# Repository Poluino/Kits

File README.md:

# WeatherStationPCB 

This repository includes all the files to print your own PCB, Source the components, and debug the circuit.

Currently we offer 4 different kits;

# Kits:
1. Barebones Kit: 
    - Temperature, Humidity, and Pressure. The three basic measurements for a home weather station project.
    - Version 1.0 Includes the BME280 sensor and an ESP32 Dev Board (30 pin).
  
2. Full Kit:
    - Temperature, Humidity, Pressure, Air Quality, Luminosity, UV Index, and Rain.
    - Version 1.2 Includes the DHT11 for Humidity, BMP280 for Pressure and Temperature, MQ - 135 for Air Quality, BH1750 for Luminosity, GUVA - S12SD for UV Index, and YL - 83 for Rain.
    - Version 2.0 Will use BME280 for Humidity, Temperature, and Humidity, VEML 6070 for UV Index. Others will remain Unchanged.
  
3. Full Kit (SMD version):
    - Basically the big boy version of the Full Kit, which uses the same sensors used by the Full Kit (V - 2.0) but will have all the components in their SMD package and will include components for a DIY ESP32 Development Board. 

4. Extended: 
    - This is for the Real DIY Weatherman. It includes a ton of high accuracy sensors for Temperature, Humidity, Pressure, Air Quality, Carbon Monoxide, Carbon Dioxide, Wind Speed, Wind Direction, Rain Gauge, UV Index, Luminosity, Soil Moisture, Ground Temperature

The PCBs for the kits were designed using the KiCad Open source software. 

# You can purchase our Kits at our Tindie Store:
 - [India](https://www.tindie.com/stores/wsp_india/)

Feel free to contact me via email at dhruv@weatherstationproject.com or via discord at DhruvS#7149.

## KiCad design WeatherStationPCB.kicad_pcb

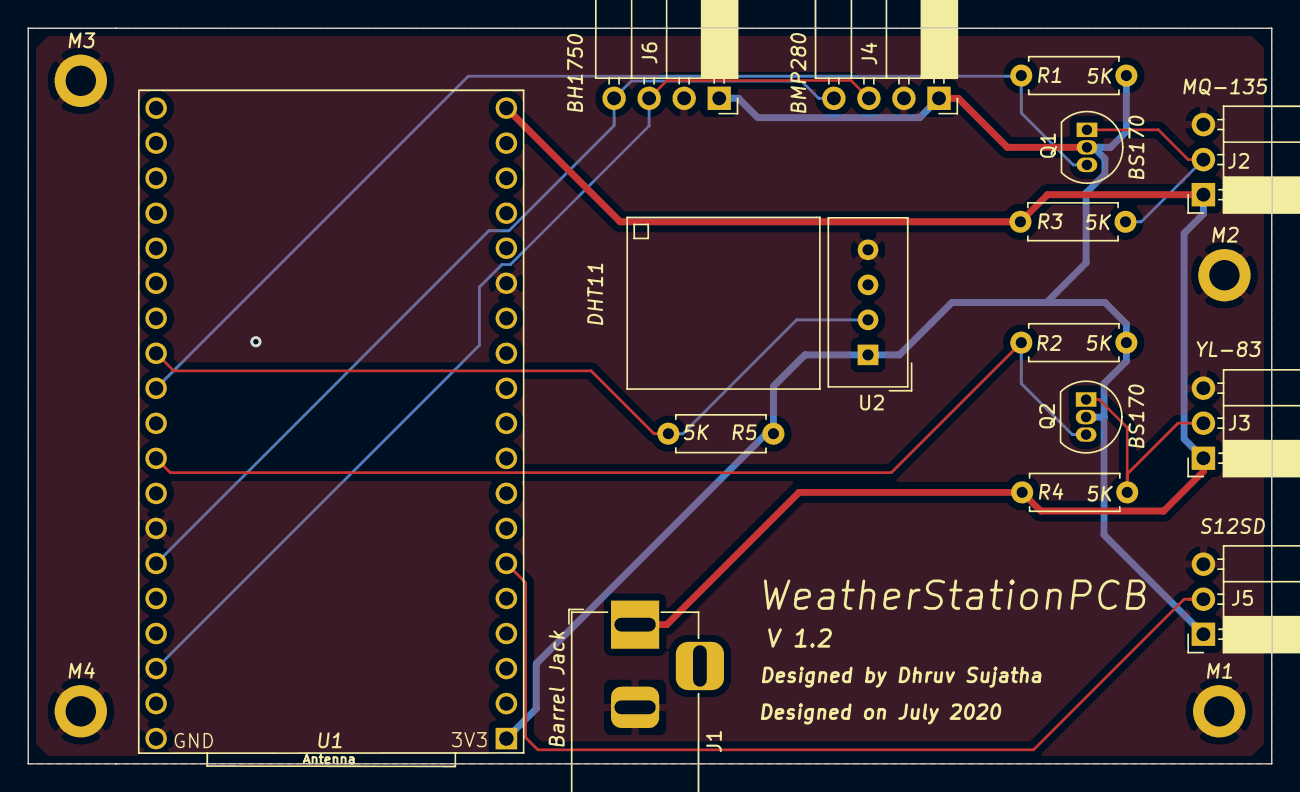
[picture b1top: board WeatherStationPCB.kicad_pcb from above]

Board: 2 copper layers, 90.2 x 53.3 mm, 19 parts (0 on the bottom side), 11 nets.

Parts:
J1: Barrel_Jack_Switch; BarrelJack_Horizontal
J2, J3, J5: Conn_01x03_Female; PinSocket_1x03_P2.54mm_Horizontal
J4: BMP280 Pressure Sensor; PinSocket_1x04_P2.54mm_Horizontal
J6: BH1750 Lux Meter; PinSocket_1x04_P2.54mm_Horizontal
M1, M2, M3, M4: MountingHole_2.2mm_M2_DIN965_Pad
Q1, Q2: BS170; TO-92_Inline
R1, R2, R3, R4, R5: 5K; R_Axial_DIN0207_L6.3mm_D2.5mm_P7.62mm_Horizontal
U1: ESP32-DEVKITC-32D; MODULE_ESP32-DEVKITC-32D
U2: DHT11; Aosong_DHT11_5.5x12.0_P2.54mm

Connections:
3V3: J4.1, J5.1, J6.1, Q1.2, Q2.2, R1.2, R2.2, R5.1, U1.1, U2.1
5V: J1.1, J2.1, J3.1, R3.1, R4.1, U1.19
DHT22Data: R5.2, U1.31, U2.2
GND: J1.2, J2.3, J3.3, J4.2, J5.3, J6.2, M1.1, M2.2, M3.3, M4.4, U1.14, U1.20, U1.26, U2.4
MQ135Data: Q1.3, R1.1, U1.30
MQ135Data5V: J2.2, Q1.1, R3.2
S12SD-UVData: J5.2, U1.6
SCL: J4.3, J6.3, U1.22
SDA: J4.4, J6.4, U1.25
YL-83Data: Q2.3, R2.1, U1.28
YL-83Data5V: J3.2, Q2.1, R4.2

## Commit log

2020-07-22 Added files (both.zip and .gbr/.drl)
2020-07-24 Added more info on ReadMe and schematic file
    Added a bried explanation on what the board is designed for, the sensors that it has, etc...
    Added the Schematic file for the PCB in .pdf format.
    Added contact info.
2020-07-24 Added source files and cleanup
    Added the .sch and .kicad_pcb files and cleaned up the existing files into folders.
2020-08-28 Updated README.md
    Grammar Errors
2020-08-31 Changed the Files layout for longevity and support for more versions of the PCB
2020-08-31 Corrected Markdown Error
2020-08-31 Updated the License
2020-08-31 Rectified Grammatical Error
2020-08-31 Added Tindie Store link
2020-08-31 test
2020-08-31 test2
2020-08-31 test3
2020-08-31 test4
2020-08-31 test5
2020-08-31 test6
2020-08-31 Added website link
2020-08-31 Updated the LICENSE Again
2020-09-01 Added Pictures Folder
2020-09-01 Added .jpg Pictures
2020-09-12 added barebones kit

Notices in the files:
WeatherStationPCB.kicad_pcb:
This project is protected by the GNU General Public License V-3.0
GPL V3.0
